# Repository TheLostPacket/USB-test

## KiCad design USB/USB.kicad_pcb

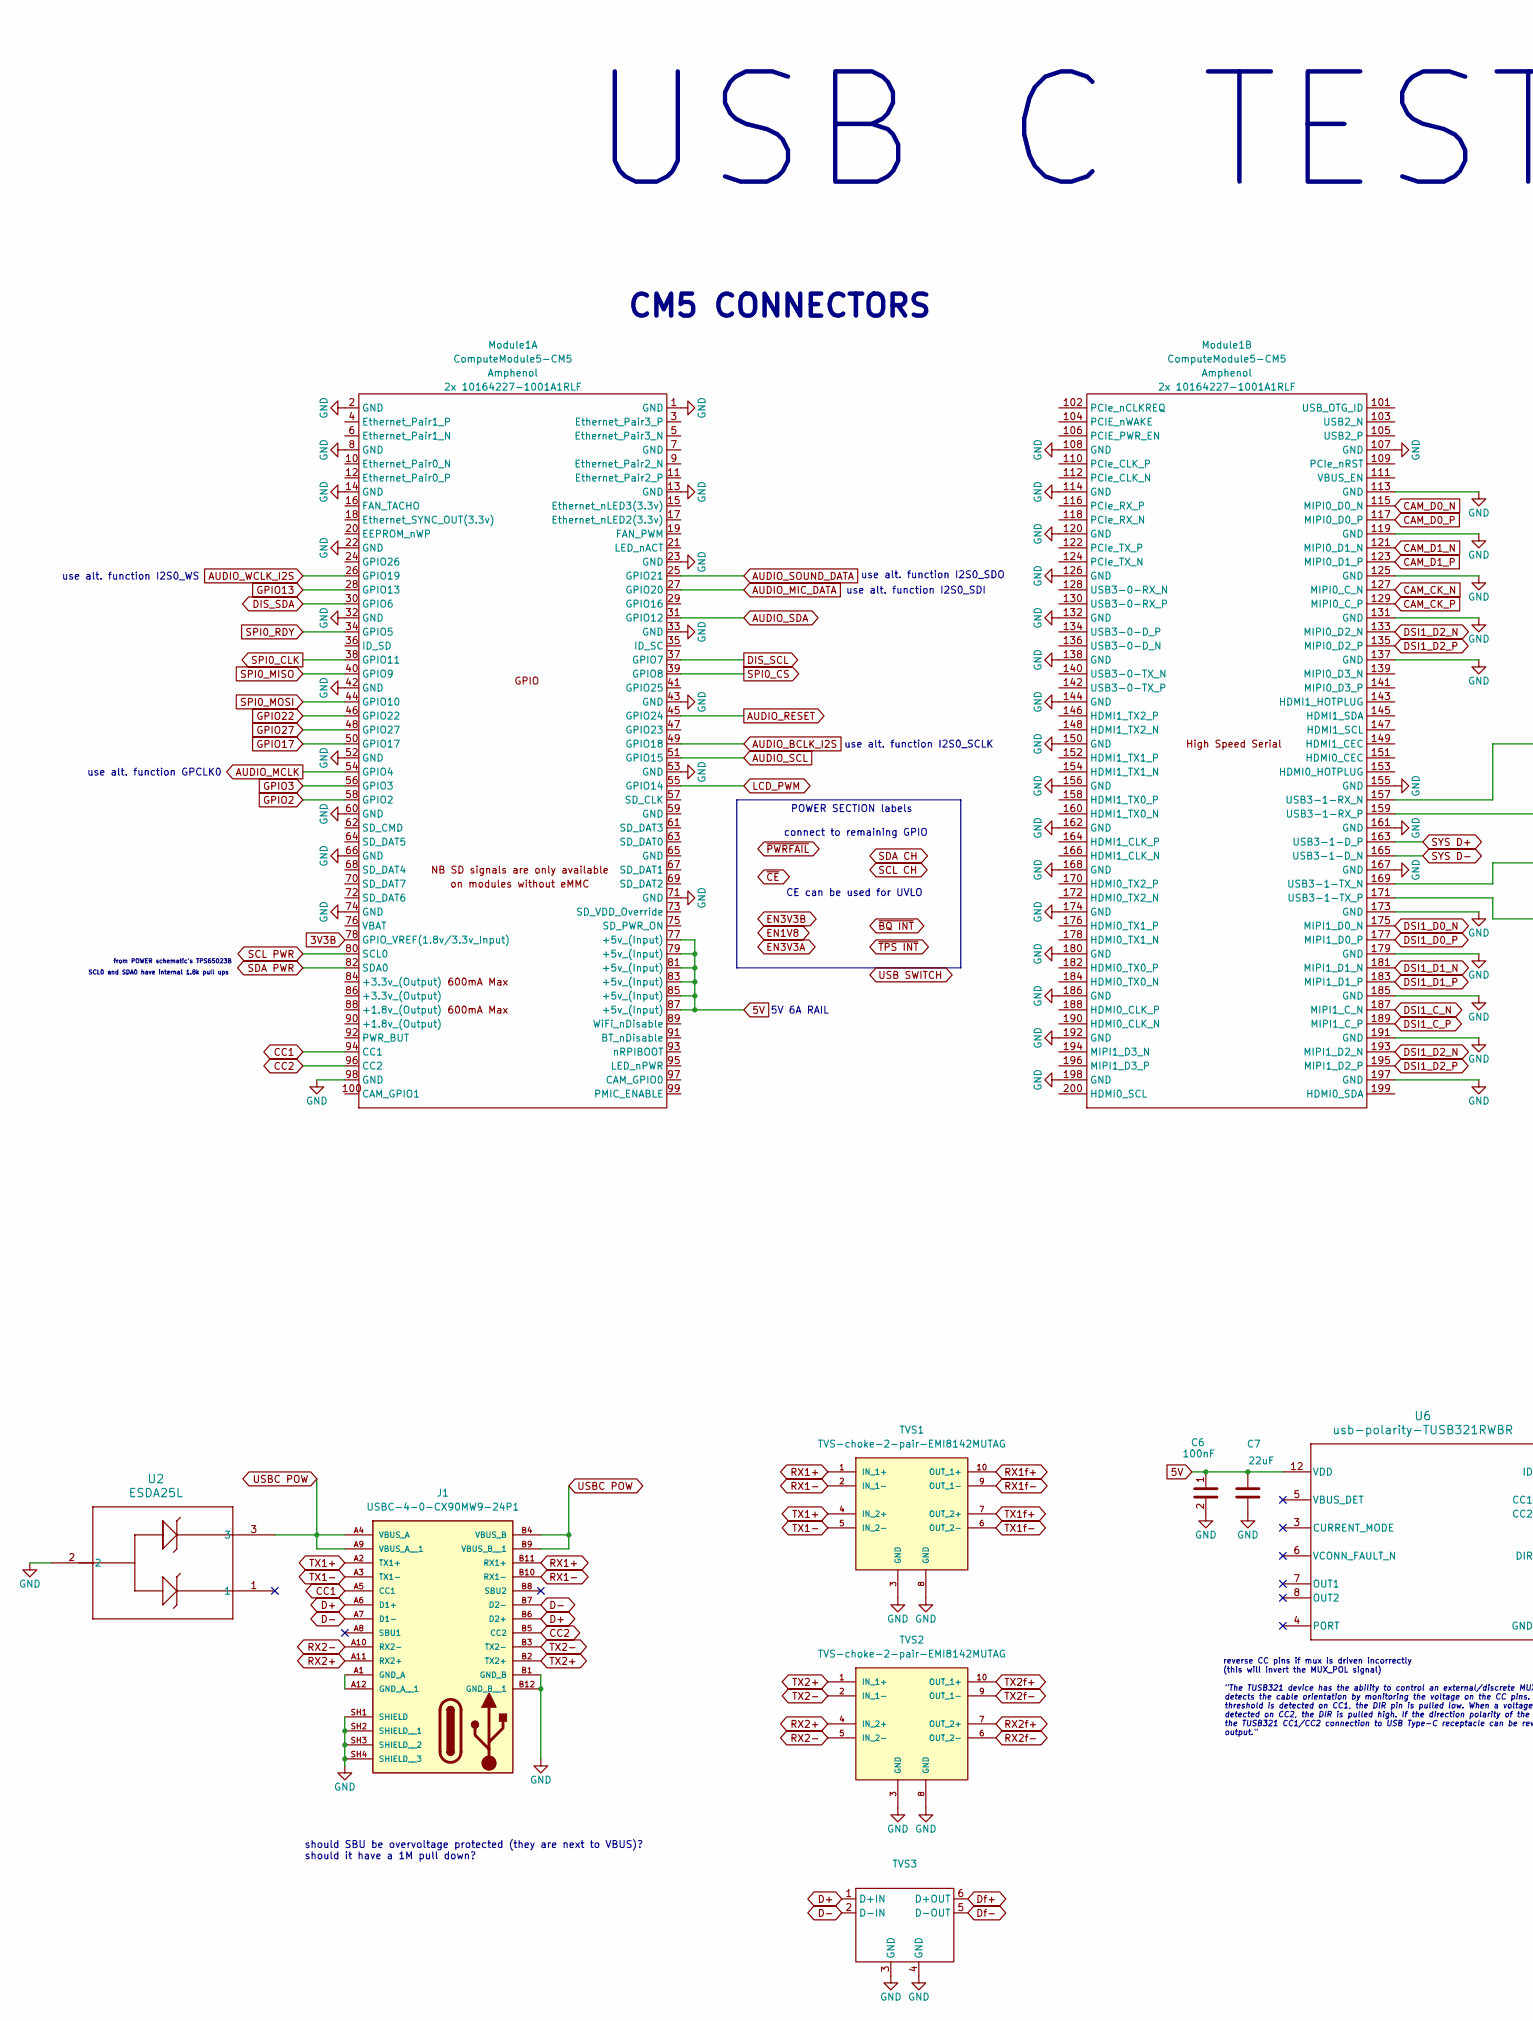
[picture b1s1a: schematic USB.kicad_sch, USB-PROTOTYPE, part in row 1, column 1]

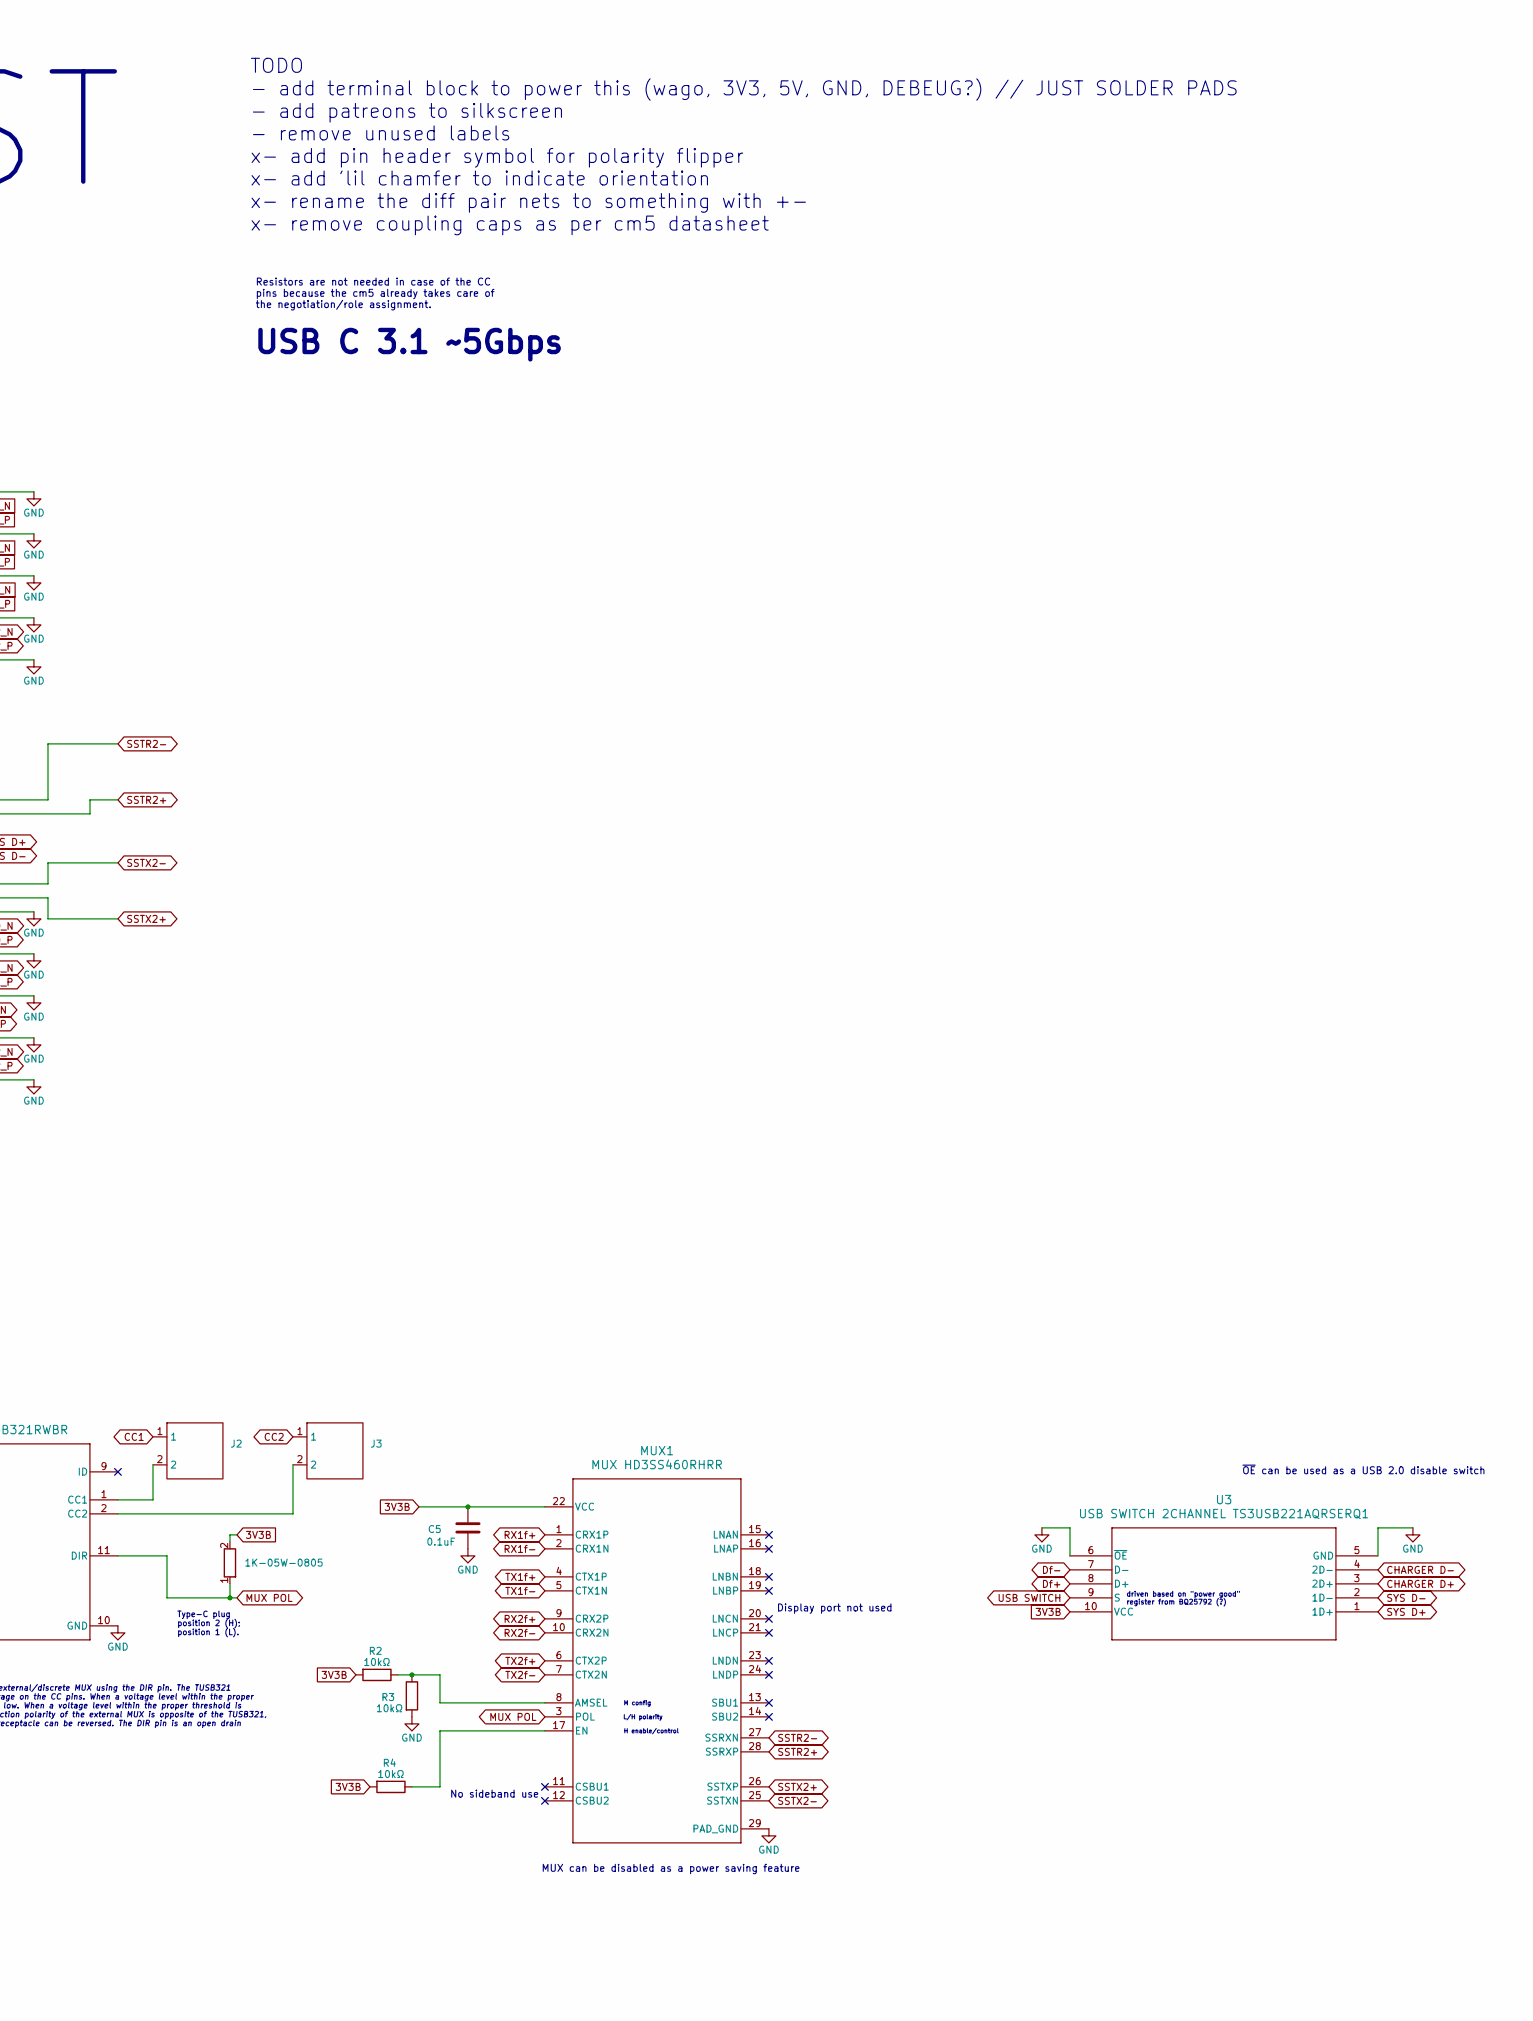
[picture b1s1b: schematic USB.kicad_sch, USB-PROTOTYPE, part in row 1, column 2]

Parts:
C5: 0.1uF; 0603-capacitor; MPN CC0603KRX7R7BB104
C6: 100nF; 0603-capacitor; MPN CC0603ZRY5V9BB104
C7: 22uF; 0603-capacitor; MPN CC0603MRX6S5BB226
J1: USBC-4-0-CX90MW9-24P1; USB-4-0-HIROSE_CX90MW9-24P1; PARTREV 24.05.01
J2, J3: PinHeader_1x02_P1.00mm_Vertical
MUX1: MUX HD3SS460RHRR; USB-MUX-RHR0028A
Module1: ComputeModule5-CM5; Raspberry-Pi-5-Compute-Module
R1: 1K-05W-0805; 0805-resistor; PARTREV 3/1/2020
R2, R3, R4: 10kΩ; 0603-resistor; MPN ERA-3AEB103V
TVS1, TVS2: TVS-choke-2-pair-EMI8142MUTAG; 2-channel-TVS-chokeXDFN10_2P2X1P3_ONS; PARTREV 0
TVS3: 1-channel-TVS-choke-XDFN6_1P2X1P2_ONS; MPN EMI8141
U2: ESDA25L; SOT-23-3; MPN ESDA25L
U3: USB SWITCH 2CHANNEL TS3USB221AQRSERQ1; USB-SWITCH-2CHANNEL-TS3USB221AQRSERQ1; MPN TS3USB221A
U6: usb-polarity-TUSB321RWBR; polarity-usb-TUSB321RWBR

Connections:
3V3B: C5.1, MUX1.22 (VCC), Module1.78 (GPIO_VREF(1.8v/3.3v_Input)), R1.2, R2.2, R4.2, U3.10 (VCC)
5V: C6.1, C7.1, Module1.77 (+5v_(Input)), Module1.79 (+5v_(Input)), Module1.81 (+5v_(Input)), Module1.83 (+5v_(Input)), Module1.85 (+5v_(Input)), Module1.87 (+5v_(Input)), U6.12 (VDD)
AUDIO_BCLK_I2S: Module1.49 (GPIO18)
AUDIO_MCLK: Module1.54 (GPIO4)
AUDIO_MIC_DATA: Module1.27 (GPIO20)
AUDIO_RESET: Module1.45 (GPIO24)
AUDIO_SCL: Module1.51 (GPIO15)
AUDIO_SDA: Module1.31 (GPIO12)
AUDIO_SOUND_DATA: Module1.25 (GPIO21)
AUDIO_WCLK_I2S: Module1.26 (GPIO19)
CAM_CK_N: Module1.127 (MIPI0_C_N)
CAM_CK_P: Module1.129 (MIPI0_C_P)
CAM_D0_N: Module1.115 (MIPI0_D0_N)
CAM_D0_P: Module1.117 (MIPI0_D0_P)
CAM_D1_N: Module1.121 (MIPI0_D1_N)
CAM_D1_P: Module1.123 (MIPI0_D1_P)
CC1: J1.A5 (CC1), J2.1, Module1.94 (CC1)
CC2: J1.B5 (CC2), J3.1, Module1.96 (CC2)
CHARGER D+: U3.3 (2D+)
CHARGER D-: U3.4 (2D-)
D+: J1.A6 (D1+), J1.B6 (D2+), TVS3.1 (D+IN)
D-: J1.A7 (D1-), J1.B7 (D2-), TVS3.2 (D-IN)
DIS_SCL: Module1.37 (GPIO7)
DIS_SDA: Module1.30 (GPIO6)
DSI1_C_N: Module1.187 (MIPI1_C_N)
DSI1_C_P: Module1.189 (MIPI1_C_P)
DSI1_D0_N: Module1.175 (MIPI1_D0_N)
DSI1_D0_P: Module1.177 (MIPI1_D0_P)
DSI1_D1_N: Module1.181 (MIPI1_D1_N)
DSI1_D1_P: Module1.183 (MIPI1_D1_P)
DSI1_D2_N: Module1.133 (MIPI0_D2_N), Module1.193 (MIPI1_D2_N)
DSI1_D2_P: Module1.135 (MIPI0_D2_P), Module1.195 (MIPI1_D2_P)
Df+: TVS3.6 (D+OUT), U3.8 (D+)
Df-: TVS3.5 (D-OUT), U3.7 (D-)
GPIO2: Module1.58 (GPIO2)
GPIO3: Module1.56 (GPIO3)
GPIO13: Module1.28 (GPIO13)
GPIO17: Module1.50 (GPIO17)
GPIO22: Module1.46 (GPIO22)
GPIO27: Module1.48 (GPIO27)
LCD_PWM: Module1.55 (GPIO14)
MUX POL: MUX1.3 (POL), R1.1, U6.11 (DIR)
unnamed: MUX1.8 (AMSEL), R2.1, R3.1
unnamed: MUX1.17 (EN), R4.1
unnamed: J2.2, U6.1 (CC1)
unnamed: J3.2, U6.2 (CC2)
RX1+: J1.B11 (RX1+), TVS1.1 (IN_1+)
RX1-: J1.B10 (RX1-), TVS1.2 (IN_1−)
RX1f+: MUX1.1 (CRX1P), TVS1.10 (OUT_1+)
RX1f-: MUX1.2 (CRX1N), TVS1.9 (OUT_1-)
RX2+: J1.A11 (RX2+), TVS2.4 (IN_2+)
RX2-: J1.A10 (RX2-), TVS2.5 (IN_2-)
RX2f+: MUX1.9 (CRX2P), TVS2.7 (OUT_2+)
RX2f-: MUX1.10 (CRX2N), TVS2.6 (OUT_2-)
SCL PWR: Module1.80 (SCL0)
SDA PWR: Module1.82 (SDA0)
SPI0_CLK: Module1.38 (GPIO11)
SPI0_CS: Module1.39 (GPIO8)
SPI0_MISO: Module1.40 (GPIO9)
SPI0_MOSI: Module1.44 (GPIO10)
SPI0_RDY: Module1.34 (GPIO5)
SSTR2+: MUX1.28 (SSRXP), Module1.159 (USB3-1-RX_P)
SSTR2-: MUX1.27 (SSRXN), Module1.157 (USB3-1-RX_N)
SSTX2+: MUX1.26 (SSTXP), Module1.171 (USB3-1-TX_P)
SSTX2-: MUX1.25 (SSTXN), Module1.169 (USB3-1-TX_N)
SYS D+: Module1.163 (USB3-1-D_P), U3.1 (1D+)
SYS D-: Module1.165 (USB3-1-D_N), U3.2 (1D-)
TX1+: J1.A2 (TX1+), TVS1.4 (IN_2+)
TX1-: J1.A3 (TX1-), TVS1.5 (IN_2-)
TX1f+: MUX1.4 (CTX1P), TVS1.7 (OUT_2+)
TX1f-: MUX1.5 (CTX1N), TVS1.6 (OUT_2-)
TX2+: J1.B2 (TX2+), TVS2.1 (IN_1+)
TX2-: J1.B3 (TX2-), TVS2.2 (IN_1−)
TX2f+: MUX1.6 (CTX2P), TVS2.10 (OUT_1+)
TX2f-: MUX1.7 (CTX2N), TVS2.9 (OUT_1-)
USB SWITCH: U3.9 (S)
USBC POW: J1.A4 (VBUS_A), J1.A9 (VBUS_A__1), J1.B4 (VBUS_B), J1.B9 (VBUS_B__1), U2.3

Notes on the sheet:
Resistors are not needed in case of the CC pins because the cm5 already takes care of the negotiation/role assignment.
POWER SECTION labels
use alt. function I2S0_WS
H enable/control
use alt. function GPCLK0
"The TUSB321 device has the ability to control an external/discrete MUX using the DIR pin. The TUSB321 detects the cable orientation by monitoring the voltage on the CC pins. When a voltage level within the proper threshold is detected on CC1, the DIR pin is pulled low. When a voltage level within 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
driven based on "power good" register from BQ25792 (?)
should SBU be overvoltage protected (they are next to VBUS)? should it have a 1M pull down?
use alt. function I2S0_SDI
Type-C plug position 2 (H); position 1 (L).
TODO - add terminal block to power this (wago, 3V3, 5V, GND, DEBEUG?) // JUST SOLDER PADS - add patreons to silkscreen - remove unused labels x- add pin header symbol for polarity flipper x- add 'lil chamfer to indicate orientation x- rename the diff pair nets to something with +- x- remove couplin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
use alt. function I2S0_SCLK
USB C TEST
connect to remaining GPIO
CE can be used for UVLO
MUX can be disabled as a power saving feature
from POWER schematic's TPS65023B
5V 6A RAIL
No sideband use
use alt. function I2S0_SDO
SCL0 and SDA0 have internal 1.8k pull ups
reverse CC pins if mux is driven incorrectly (this will invert the MUX_POL signal)
M config
L/H polarity
USB C 3.1 ~5Gbps
~{OE} can be used as a USB 2.0 disable switch
CM5 CONNECTORS
Display port not used

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
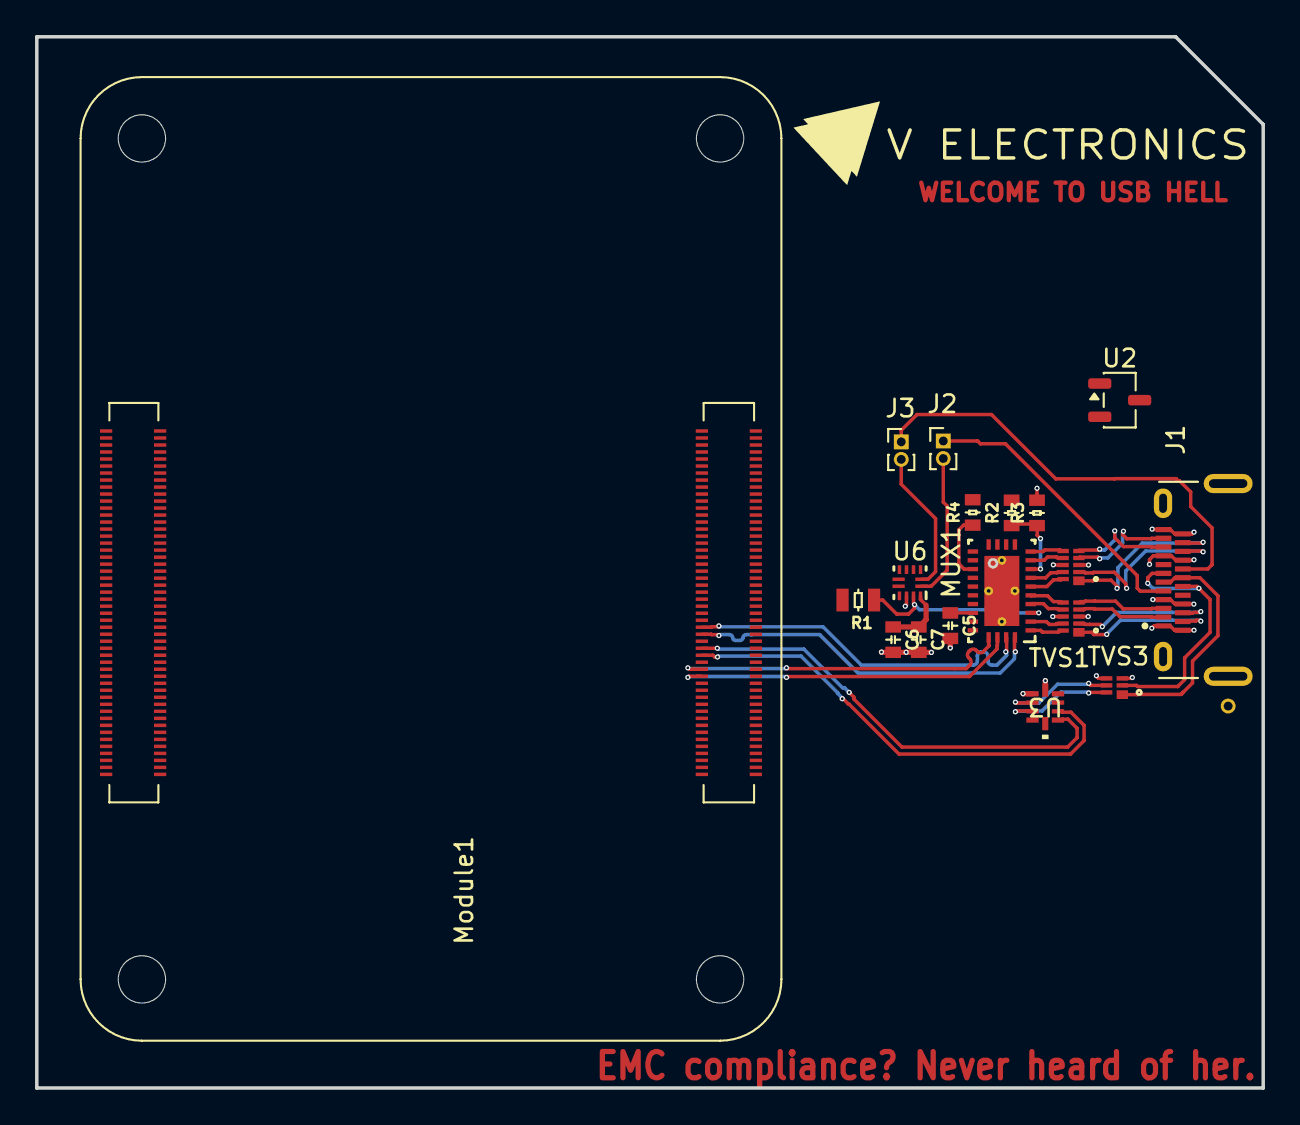
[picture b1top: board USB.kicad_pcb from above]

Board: 4 copper layers, 70.0 x 60.0 mm, 18 parts (0 on the bottom side), 39 nets.

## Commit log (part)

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2026-05-19 fix symbols of TVS chokes
2026-05-19 add tvs choke footprints and 3D models
2026-05-19 add MPNs and datasheet
